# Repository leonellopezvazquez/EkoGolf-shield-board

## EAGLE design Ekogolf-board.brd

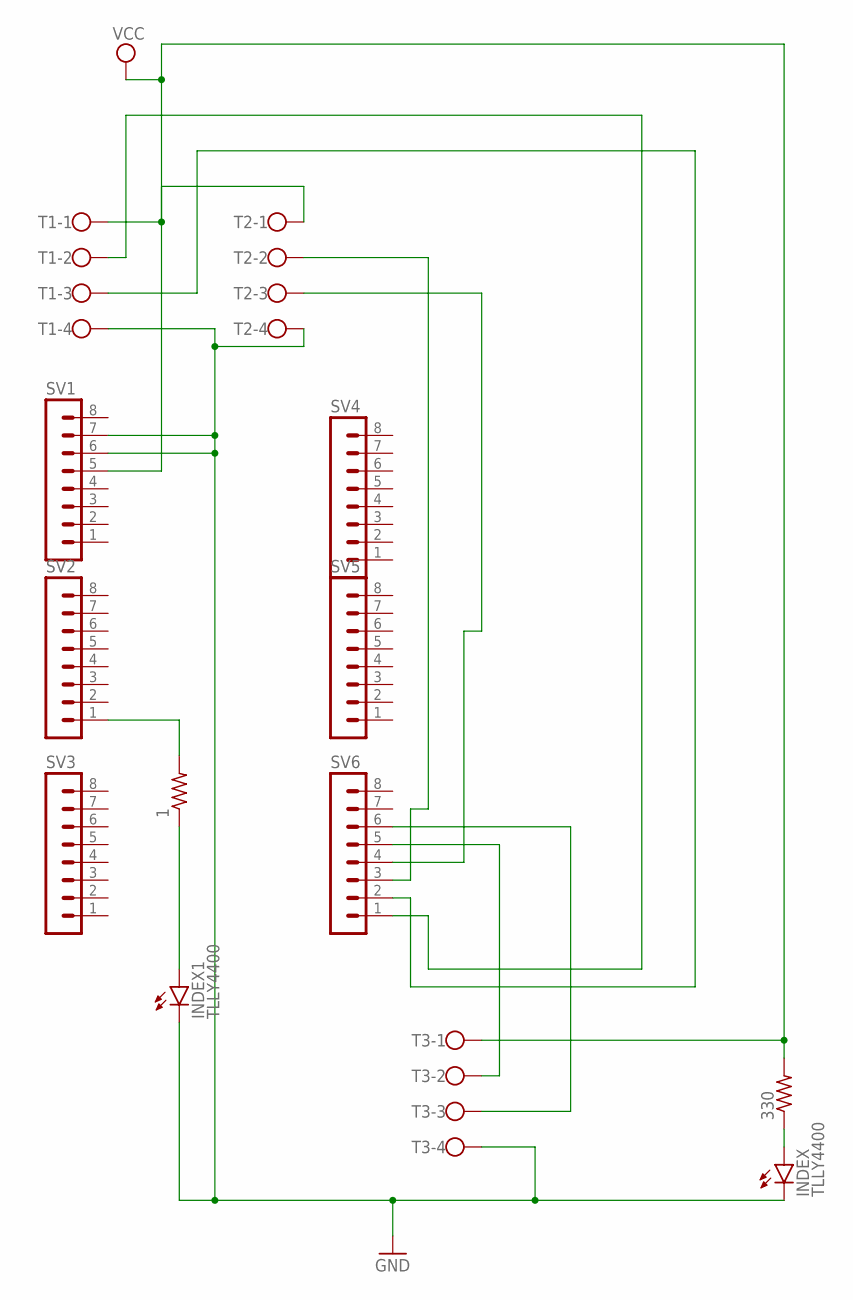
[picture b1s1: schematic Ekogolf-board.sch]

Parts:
1, 330: R-US_0204/5; 0204/5
INDEX, INDEX1: TLLY4400; LED3MM
SV1, SV2, SV3, SV4, SV5, SV6: MA08-1
T1, T2, T3: W237-4

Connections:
GND: INDEX.K (C), INDEX1.K (C), SV1.6, SV1.7, T1.4, T2.4, T3.4
unnamed: 330.1, INDEX.A
unnamed: 1.2, SV2.1
unnamed: 1.1, INDEX1.A
unnamed: SV6.4, T2.3
unnamed: SV6.3, T2.2
unnamed: SV6.2, T1.3
unnamed: SV6.6, T3.3
unnamed: SV6.5, T3.2
TX3: SV6.1, T1.2
VCC: 330.2, SV1.5, T1.1, T2.1, T3.1

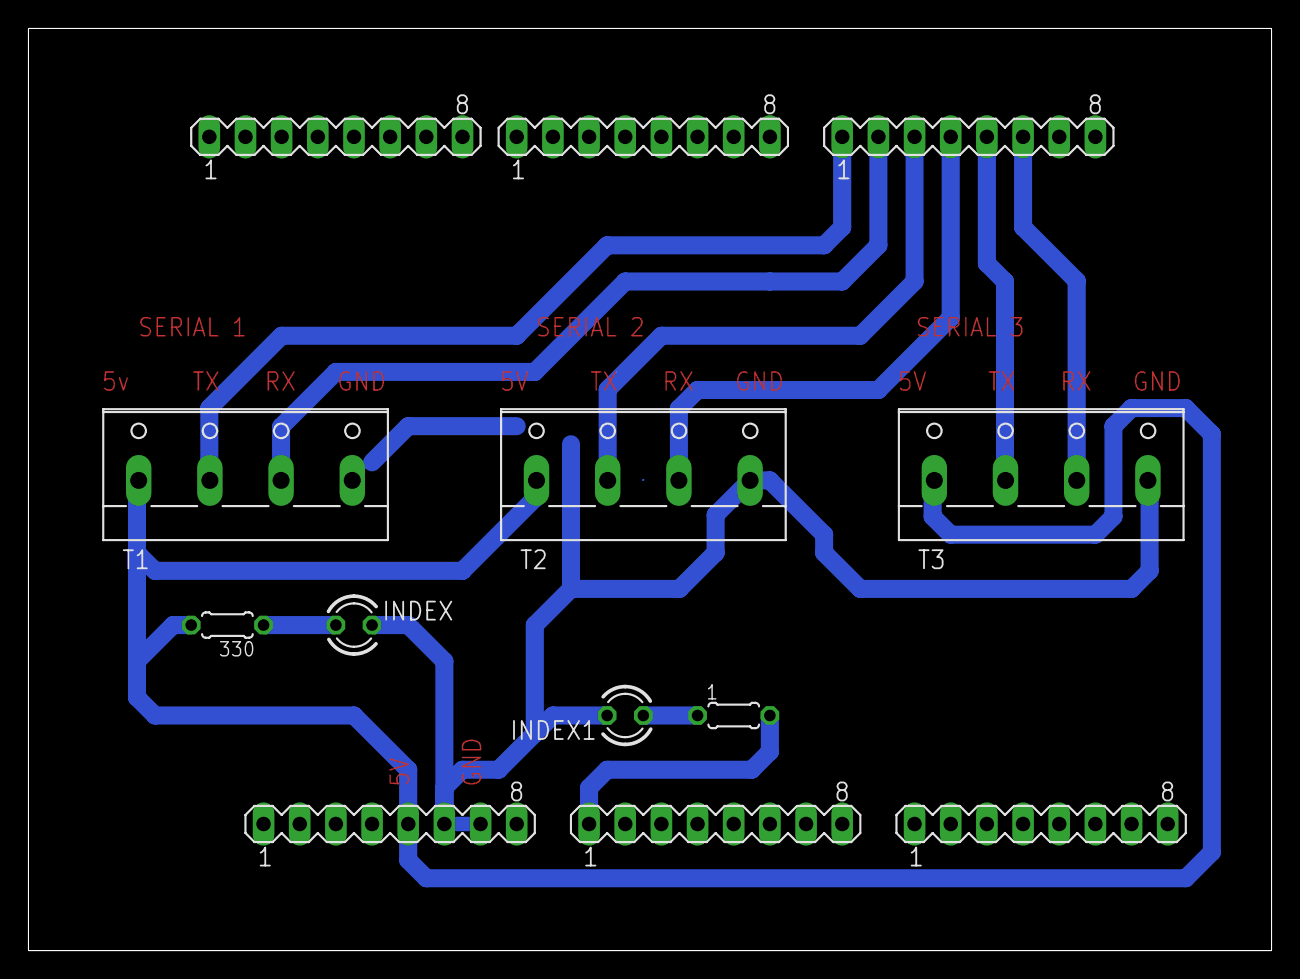
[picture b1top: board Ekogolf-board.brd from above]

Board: 2 copper layers, 87.3 x 64.8 mm, 13 parts (0 on the bottom side), 11 nets.

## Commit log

2019-07-18 first commit board
2019-07-18 four 8 pin headers
2019-07-18 some componentes, serial terminals
2019-07-18 serial terminals
2019-07-18 first routing
2019-07-22 Poligono de Masa a GND
2019-07-23 somo titles
2019-07-25 se agrega led indicador
